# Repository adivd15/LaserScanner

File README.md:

# LaserScanner
College Optoelectronics Project

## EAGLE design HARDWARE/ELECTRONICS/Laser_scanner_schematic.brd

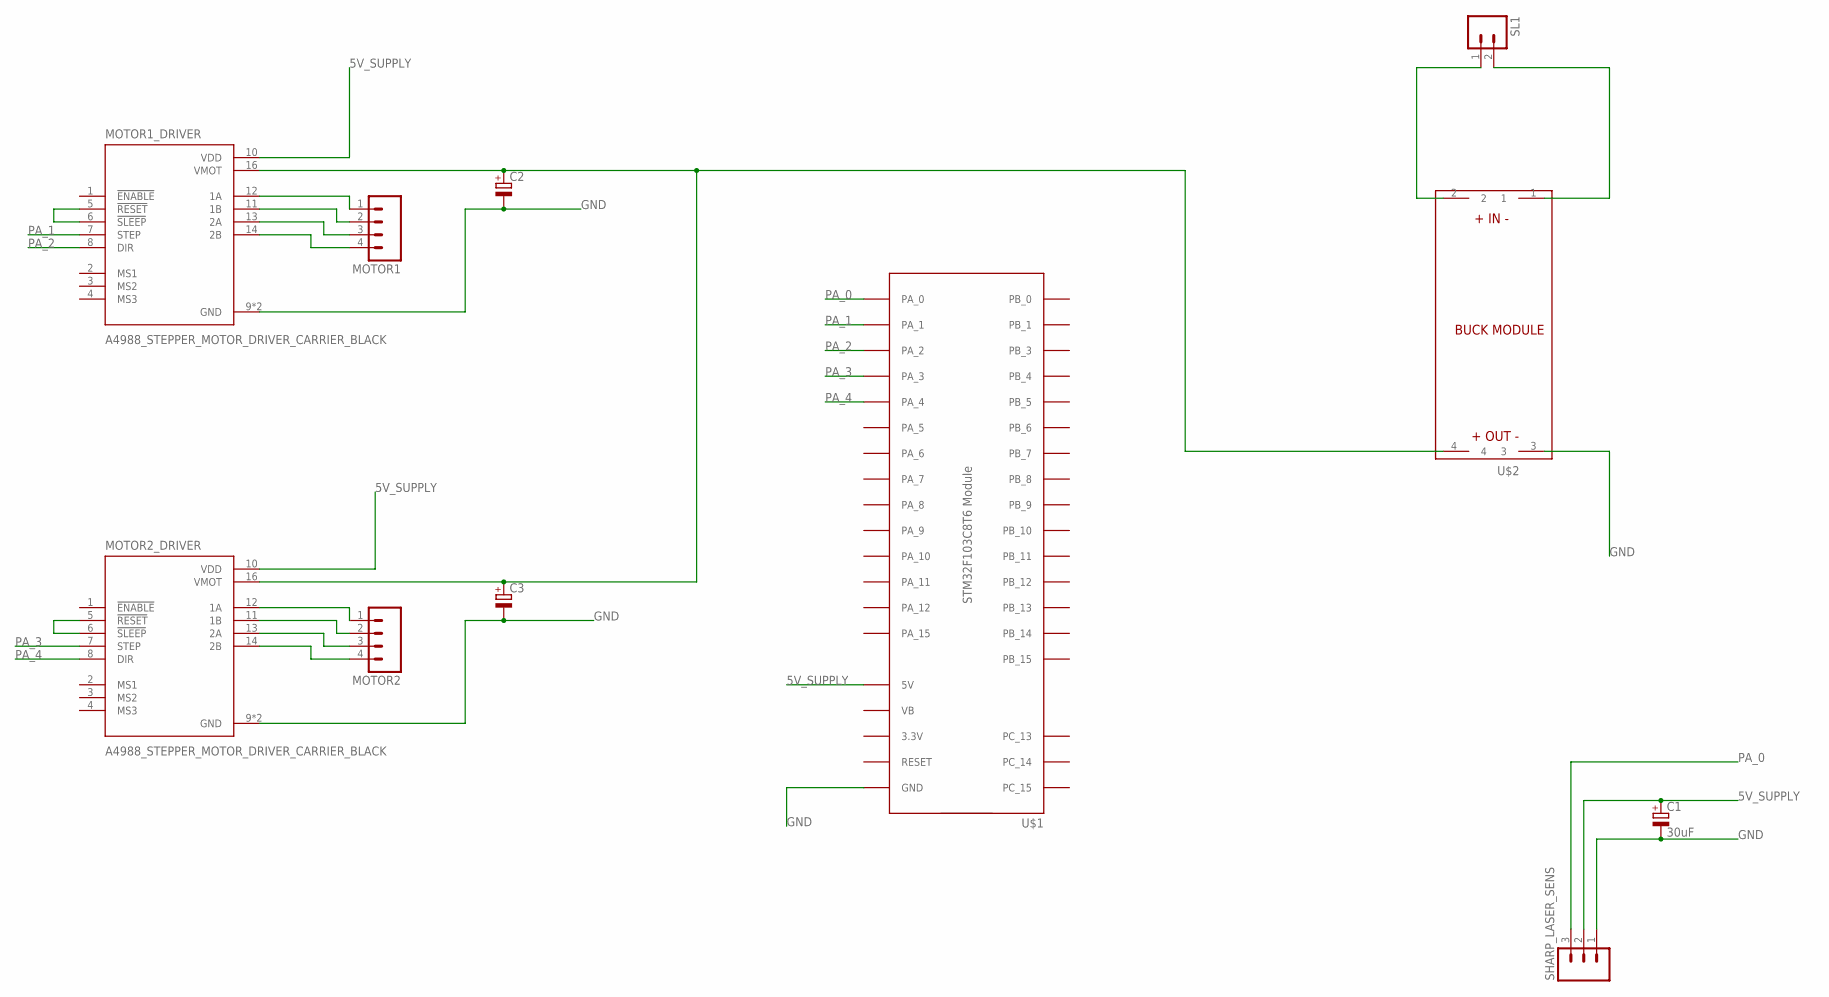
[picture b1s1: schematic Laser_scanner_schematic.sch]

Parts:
C1: 30uF; E2-4
C2, C3: CPOL-EUE2-5; E2-5
MOTOR1, MOTOR2: M04; 04P
MOTOR1_DRIVER, MOTOR2_DRIVER: A4988_STEPPER_MOTOR_DRIVER_CARRIER_BLACK; MODULE_A4988_STEPPER_MOTOR_DRIVER_CARRIER_BLACK
SHARP_LASER_SENS: M03; 03P
SL1: M02; 02P
U$1: STM32F103C8T6-MODULE
U$2: BUCK_MODULEWITH_SMDPADS&THROUGHHOLES; BUCK_MODULE

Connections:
5V_SUPPLY: C1.+, MOTOR1_DRIVER.10 (VDD), MOTOR2_DRIVER.10 (VDD), SHARP_LASER_SENS.2, U$1.5V
GND: C1.-, C2.-, C3.-, MOTOR1_DRIVER.9 (GND), MOTOR1_DRIVER.15 (GND), MOTOR2_DRIVER.9 (GND), MOTOR2_DRIVER.15 (GND), SHARP_LASER_SENS.1, U$1.GND@1 (GND), U$1.GND@2 (GND), U$1.GND@3 (GND), U$2.3
unnamed: MOTOR1.1, MOTOR1_DRIVER.12 (1A)
unnamed: MOTOR1.2, MOTOR1_DRIVER.11 (1B)
unnamed: MOTOR1_DRIVER.5 (!RESET), MOTOR1_DRIVER.6 (!SLEEP)
unnamed: MOTOR2_DRIVER.5 (!RESET), MOTOR2_DRIVER.6 (!SLEEP)
unnamed: MOTOR1.3, MOTOR1_DRIVER.13 (2A)
unnamed: MOTOR1.4, MOTOR1_DRIVER.14 (2B)
unnamed: MOTOR2.1, MOTOR2_DRIVER.12 (1A)
unnamed: MOTOR2.2, MOTOR2_DRIVER.11 (1B)
unnamed: MOTOR2.3, MOTOR2_DRIVER.13 (2A)
unnamed: MOTOR2.4, MOTOR2_DRIVER.14 (2B)
unnamed: SL1.1, U$2.2
unnamed: SL1.2, U$2.1
unnamed: C2.+, C3.+, MOTOR1_DRIVER.16 (VMOT), MOTOR2_DRIVER.16 (VMOT), U$2.4
PA_0: SHARP_LASER_SENS.3, U$1.PA_0
PA_1: MOTOR1_DRIVER.7 (STEP), U$1.PA_1
PA_2: MOTOR1_DRIVER.8 (DIR), U$1.PA_2
PA_3: MOTOR2_DRIVER.7 (STEP), U$1.PA_3
PA_4: MOTOR2_DRIVER.8 (DIR), U$1.PA_4

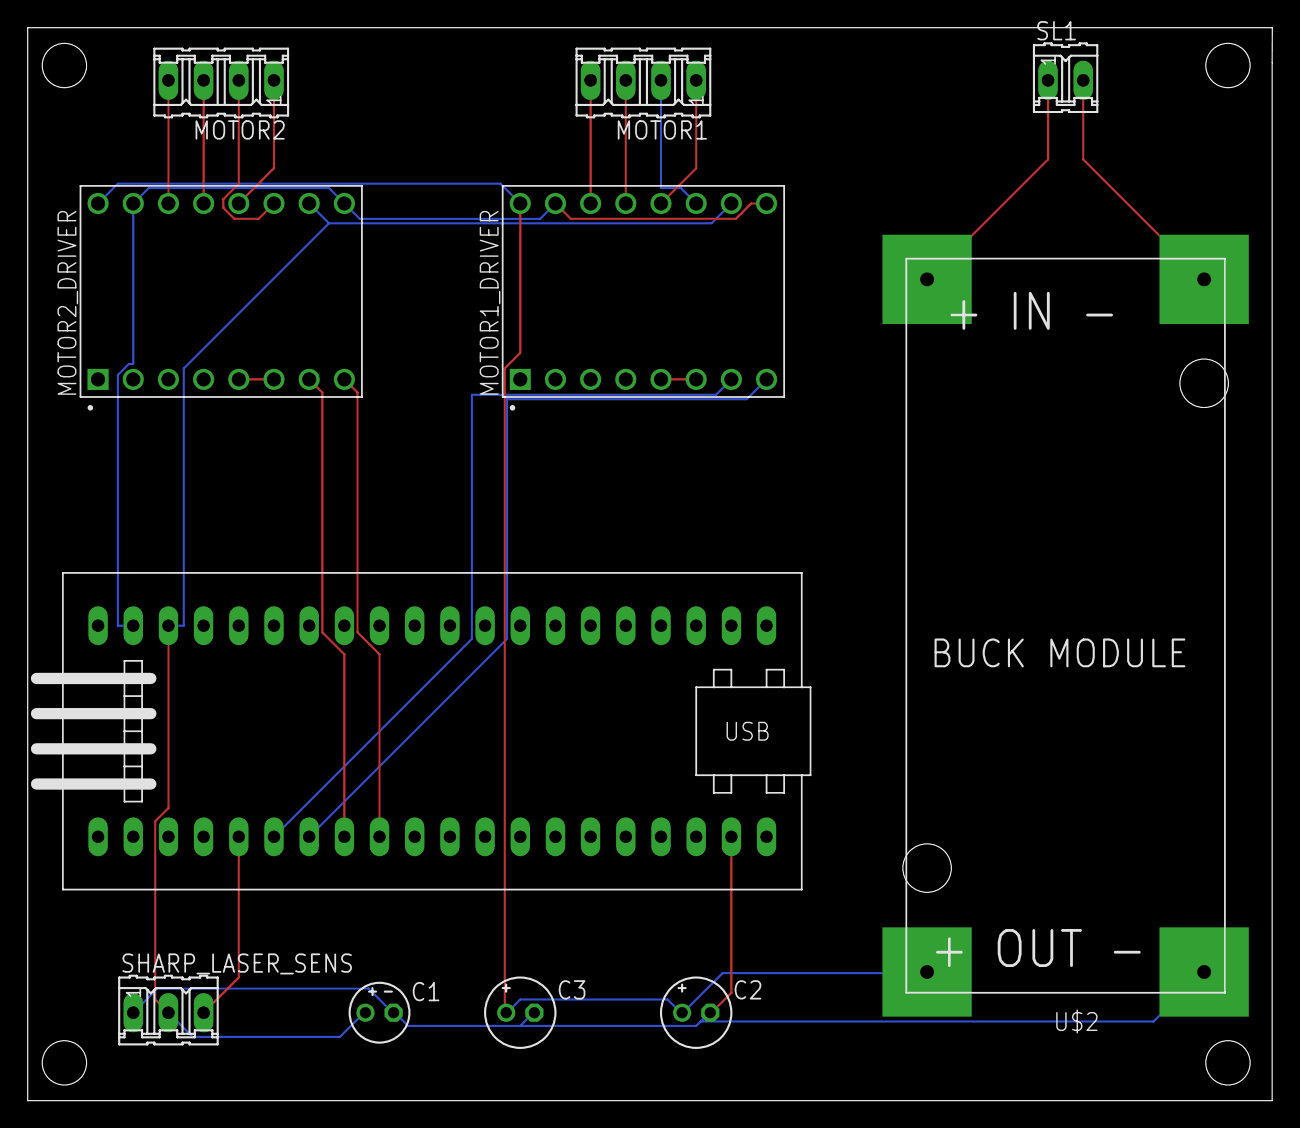
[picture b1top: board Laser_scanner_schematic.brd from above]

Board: 2 copper layers, 89.9 x 77.5 mm, 11 parts (0 on the bottom side), 20 nets.

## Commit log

2022-10-03 Created component list
2022-10-03 Modified sharp sensor price
2022-10-04 Generated basic software
2022-10-10 ordered some componenets and modified shopping list
2022-10-17 Managed USB comm
2022-10-17 Managed to read sensor distance
2022-10-19 Managed to spin motor
2022-10-19 Created static design
2022-10-24 finished electronics pcb design
2022-10-30 Created scanner base
2022-11-03 Worked on srv_motor_controll
2022-11-03 Fixed motor port selection
2022-11-04 tests
2022-11-04 Created base for 3d scanner
2022-11-09 Made plate 3d printable
2022-11-10 added screw holes
2022-11-10 modified 3d printable file
2022-11-10 cut base in half
2022-11-15 updated base sensor holder part and made stl of second half of base
2022-11-16 added holes to seond half of base
2022-11-16 Created sensor mount plate
2022-12-04 finished design
2022-12-04 deleted not necesarry files
2022-12-08 finished motor_control_module
2022-12-08 Added srv_sens_module
2022-12-14 Worked on sens_library
2022-12-16 Finished sensor library
2022-12-16 fixed some errors and changed prj name
2022-12-18 Finished release
2022-12-18 Added docs
